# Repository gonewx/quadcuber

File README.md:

> 最终机械版：**501 步、882 件**（64 件底盘＋668 件四臂＋150 件支承与重力复位杠杆）。
> [整机 3D](generated/site/index.html) · [501 步组装](generated/site/integrated-assembly.html) · [完整 PDF](generated/mechanical/manual/manual.pdf) · [最终 BOM](generated/mechanical/final-BOM.csv) · [生成源码与重建](mechanical/README.md)
> **GitHub 仓库为主源码，Sites 仅用于发布。** 当前机械设计见 `mechanical/`；早期 v4 改装资料保留用于历史追溯。实体装配、承载、重力回落与带电联锁仍待验收。

# quadcuber

四机械手乐高魔方机器人（参考 CubeStormer 3 的思路），目前包含**动作规划器**、**模拟器**，以及**单臂原型的 Pico 测试程序**。

* 规划器：把求解器给出的转动序列（如 `R U R' U'`）翻译成 4 个机械手的动作序列，并使总耗时最短。

* 模拟器：在 54 个贴纸的魔方模型上按物理动作逐步重放，检查每一步是否满足机械约束，以及最后魔方是否还原。

* 单臂测试程序（`firmware/pico/`，MicroPython）：测机械手转 90° 的耗时、到位精度和夹持可靠性，结果汇总后替换规划器的耗时估算值。接线和测试步骤见 [docs/single\_arm.md](docs/single_arm.md)，乐高机械手的结构思路和尺寸要求见 [docs/arm\_concept.md](docs/arm_concept.md)，**搭建说明书**见 [generated/site/integrated-assembly.html](generated/site/integrated-assembly.html)（501 步最终整机版，总入口 [docs/lego/index.html](docs/lego/index.html)）。

规划器纯 Python 实现，不依赖第三方库，可以在 PC 或树莓派 Zero W 上运行。

## 电路与硬件验证

当前手焊板为 **[B1 底板](electronics-b1/README.md)**：99×99mm 双层板，插装 Pico H，其余元件手焊。PCB 和零件已到手，按 **[B1 焊接与首次上电指南](docs/b1-soldering-guide.md)** 装配，配合[元件位置图](generated/electronics-b1/assembly.png)和[手焊 BOM](generated/electronics-b1/bom-hand-solder.csv)。焊接、编码器电平、供电及带载仍待实测。

[A1 集成板](electronics/README.md)及其[工程首板送厂包](generated/electronics/engineering-first-board/README.md)保留作历史资料；其板载 RP2040、双面 SMT、自焊18件和专用固件流程不适用于 B1。

打开[当前接线：原 R／新 R+L（条件式）](generated/wiring/direct-breadboard.html)，在同一页面切换图、表和下载，默认显示原 R。适用条件见[电路总览](docs/wiring/README.md)；[历史单臂总览](generated/wiring/index.html)和[可选单臂洞洞板](generated/wiring/perfboard.html)保留作参考。EV3 大马达＋DRV8833 的空载闭环已通过，范围见[实测记录](docs/single_arm-results.md)；这不等于 v4 机械头、舵机、带魔方动作或四臂供电已验收。接下来需要实物标定和分级测试。

当前硬件：EV3 大马达、DRV8833（名义 9V，实测不得超过 10.8V）、每路 10kΩ/20kΩ 编码器分压（`ENC_PULLUP = False`）、灰色 270° Geekservo。调试时 Pico 由 USB 供电，舵机由独立 5V 降压供电，所有模块共地。接线以 `wiring/spec.py` 及其生成图表为准。

固件的开／合端点及安全工作区间（`SERVO_OPEN_US`、`SERVO_CLOSE_US`、`SERVO_MIN_US`、`SERVO_MAX_US`）默认均为 `None`，`SERVO_CALIBRATED = False`。未完成实物标定时，普通动力命令会拒绝执行；仅在确认无魔方、机构全行程自由且供电接线已核验后，可显式进入 `motor_test unloaded` 做空载马达验证，该模式不允许舵机开合或带载测试。按[单臂标定步骤](docs/single_arm.md#servo-calibration)先脱开连杆、声明手动会话，再逐步测量舵机端点及安全区间，最后人工记录 `v4`／`R` 标定身份并启用标志。启动不发送舵机脉冲，但不能保证上电硬件不抖动；旧脉宽和 CAD 角度不能充当实测值。

舵机时序另行确认：默认 `SERVO_MOVE_MS = None`、`SERVO_TIMING_CONFIRMED = False`。端点、安全区间和身份确认后，人工选定保守的临时等待时长（1～5000ms 整数，不沿用旧 120ms），仅用单次 `open` / `close` 录像测量，确认完全停稳才发下一条。此时 `grip`、`cycle` 和普通旋转仍被锁定，显式空载马达模式是例外。实测完整开／合的较慢值加余量后回填等待时间、设置 `SERVO_TIMING_CONFIRMED = True`，上传并 Ctrl+D 重载，才进入连续及联合测试；机构或供电变化后重新确认。

```bash
python wiring/build.py          # 生成全部电路文档及图纸
python wiring/build.py --check  # 检查配置、网络和生成文件是否同步
```

## 机器模型

```
        B
        |
  L --[魔方]-- R      U 面朝上（留给摄像头），D 面朝下；这两个面没有机械手
        |
        F
```

* 4 个机械手分别位于 R / L / F / B 方向，每个机械手可以**夹紧 / 松开**，也可以**旋转**（90° 的整数倍）。
* 夹爪是一根横跨面中间一行或一列的“夹条”。机械手角度为偶数（包括 0）时夹条竖直，为奇数时水平。
* 约束（实现见 `quadcuber/machine.py` 的 `Machine.check`）：
  1. **支撑**：任何时刻 L、R 都夹紧，或 F、B 都夹紧，否则魔方会掉落。
  2. **拧面**：拧某个面时，与它垂直且夹紧的机械手，夹条必须竖直，否则会挡住转动；并且至少有一个这样的机械手夹紧，用来固定中间层。相对的两个面可以在同一步同时拧。
  3. **整体翻转**：一对机械手夹紧并同向旋转，把 U/D 面换到有机械手的位置；此时另一对必须松开。
  4. **空转**：松开的机械手可以旋转来调整夹条方向，并且可以和其他动作同时进行。
  5. **相邻臂避碰（v4 必须）**：相邻两臂不能同时水平；任一臂旋转时，相邻两臂必须保持竖直且不在同一步旋转。拧面、空转、整体翻转以及经过水平位置的 180° 动作都适用，松开夹爪不能解除这条约束。
  6. **角度限制（可选）**：`angle_limit` 默认仍为 `None`。v4 舵机固定在平台上，不随机械头转动，不因舵机缠线强加角度上限。其他需要累计角度边界的结构可显式使用 `--angle-limit`。

`Machine()` 和 CLI 的 `plan` / `bench` 默认使用 `profile="v4"`，强制启用 `no_adjacent_horizontal=True`，不能在 v4 profile 下显式关闭。`Machine(profile="generic")` / `--profile generic` 保留旧抽象模型，仅供明确的非 v4 用途；generic 仍可用 `--no-adjacent-horizontal` 增加约束。规划器的检查不代替实物避让、刚度、保持力与耗时标定。

## 使用

```bash
# 规划一个转动序列，并在模拟器中验证
python -m quadcuber plan "R U R' U' F2 D"

# 同时输出 JSON，供下位机（Pico）执行
python -m quadcuber plan "R U R' U'" --json plan.json

# 随机 20 步序列的统计，--compare 同时对比“不做任何并行”的基准方案
python -m quadcuber bench --count 20 --compare

# 使用实测的动作耗时
python -m quadcuber bench --timing timing.json

# 仅用于非 v4 结构的旧抽象模型；不要用它驱动当前 v4
python -m quadcuber plan "R U R' U'" --profile generic
# generic 也可显式启用更严格的相邻臂约束
python -m quadcuber bench --profile generic --no-adjacent-horizontal
```

`timing.json` 的字段见 `quadcuber/machine.py` 中的 `Timing`，单位为秒。**默认值是估算值**，搭好单臂原型后应替换成实测值（可以用 `python -m quadcuber armlog arm.log -o timing.json` 从单臂测试日志生成）：

```json
{"turn90": 0.18, "turn180": 0.30, "open": 0.10, "close": 0.10,
 "rotate90": 0.15, "rotate180": 0.25, "cube90": 0.22, "cube180": 0.35}
```

## 规划算法

* 在（已完成的转动，机器状态）空间中做 A\* 搜索，代价为总耗时。每一步是一组同时执行的动作。
* 连续的同轴转动（例如 `R L'`）会合并为一组，可以按任意顺序执行，也可以同时执行。
* 默认使用**滚动窗口**：每次对接下来的 4 组转动求最优，只采用前 2 组的动作。实测比全局最优（`--full`）只慢 1~2%，但速度快得多。
* 有角度限制时，先按不限角度规划，再用动态规划选择旋转方向（必要时顺带退绕）；只有无法满足限制的窗口才做完整的受限搜索。

历史旧抽象模型在开发机上的测量（30 个随机 20 步序列、估算耗时参数，未包含当前默认的 v4 相邻臂约束；不是 v4 实物数据）：

| 情况 | 动作总耗时（平均） | 规划 CPU 时间（平均） |
| --- | --- | --- |
| 不限角度 | 7.9 s | 0.8 s |
| 角度限制 ±180° | 8.0 s | 11 s |

角度受限时规划仍然偏慢，树莓派 Zero W 上预计还要慢一个数量级。建议优先采用不需要角度限制的夹爪结构。

## 测试

```bash
python -m unittest -v
```

测试覆盖：魔方模型、各条机器约束，以及随机序列经规划后能在模拟器中还原；Pico 固件在模拟环境（马达模型 + PIO 解释器，`tests/pico_sim.py`）中的编码器计数、位置控制和各条测试命令；日志汇总工具。

## 目录

| 路径 | 内容 |
| --- | --- |
| `quadcuber/cube.py` | 贴纸魔方模型、转动记号解析 |
| `quadcuber/machine.py` | 机器状态、动作、约束、耗时参数 |
| `quadcuber/planner.py` | 动作规划器 |
| `quadcuber/simulate.py` | 模拟器 / 验证 |
| `quadcuber/armlog.py` | 单臂测试日志汇总，生成 `timing.json` |
| `quadcuber/__main__.py` | 命令行 |
| `firmware/pico/` | 单臂测试程序（MicroPython）：配置、PIO 编码器、马达/舵机驱动、位置控制、串口命令行 |
| `docs/single_arm.md` | 单臂原型的接线、测试步骤和待验证假设 |
| `docs/arm_concept.md` | 乐高机械手的概念设计：叉子 + 滑块结构、关键尺寸、单臂测试的魔方固定方法 |
| `electronics/`、`generated/electronics/` | 四臂集成 PCB 的 KiCad 源码、BOM、检查与制造预览 |
| `wiring/`、`generated/wiring/` | 接线规范和生成程序；对应标准图纸输出 |
| `docs/perfboard.md` | 可拔插洞洞板设计：逐孔安装、镜像焊接图、模块排针座及上电验收 |
| `docs/lego/` | 库存和兼容导航；历史原件通过固定 Git 提交查阅 |
| `mechanical/`、`web/`、`tools/` | 机械／网页源码及少量打包、重建入口 |
| `mechanical/` | 最终机械模型、501 步图解与 PDF、生成器、离线阅读器和 Sites 页面源码 |
| `tests/` | 控制及最终机械一致性测试 |

## Prompts

* gpt-6-astra high

现在的设计还是不理想, 设计结构复杂,但实际效果看着也不行. 我有思路需要你评估和验证: 需要在上一版本整体结构上主要优化方向是推杆到夹指的传力,要能将舵机的力量传递到夹指前端, 而不是像现在这样中间的连接是无摩擦销,导致力量无法传递, 所有现在的夹指整体的平行的设计理念 ,也导致总是间隙, 因为乐高结构和尺寸决定了现在这样的设计必然无法夹紧. 所以夹紧状态应该是现在的夹指部分不用完全 平行于魔方, 但夹指前端必须有新的结构件能自然贴合魔方, 达到夹紧的效果.

## 源码与输出

`mechanical/`、`wiring/`、`electronics/`、`web/` 分别维护机械、接线、集成PCB和网页源码；`generated/` 保存唯一标准输出；`dist/` 为不入 Git 的网站／离线／源码包。`docs/` 保存人工说明及原始实测证据，`tests/` 保存回归与独立基准；运行库 `quadcuber/` 和固件 `firmware/` 原位保留，不新增 `src/`。

运行 `python tools/build_distribution.py` 后可打开离线包，或从仓库根启动 `python -m http.server 8000` 浏览 `generated/site/index.html`。网站下载提供紧凑源码／模型包；图解与 PDF 另下。`dist/downloads/quadcuber-source-complete.zip` 是含完整图解的独立重建包；构建不发布。历史方案见 [历史索引](docs/history.md)。

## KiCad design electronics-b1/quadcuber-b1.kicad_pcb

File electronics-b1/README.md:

# B1 底板（KiCad 工程）

方案和取舍见 [docs/b1-carrier-board.md](../docs/b1-carrier-board.md)。本目录是 B1 唯一的源文件目录，与 A1（`../electronics/`）完全独立，不引用 A1 的库文件。

- 2 层 FR-4，99×99mm，1.6mm，1oz。元件全部放在顶面，尽量用贴片件（0805 及以上、SOIC/SOT-223/TO-263/HSOP），自己用热风枪和烙铁手焊。只有排针、Pico 排母、DC 插座和 EV3 插座是通孔件。
- 树莓派 Pico H 插在两排 1×20 排母上，USB 朝板子上边。引脚与 `wiring/spec.py` 的 `ARMS` 一致，固件不用改。
- 四个 EV3 插座在下边，从左到右依次是 R / L / F / B。每个插座上方是该臂的舵机排针，自下而上为 G / + / S。
- 接口丝印（2026-10-20 补）：舵机排针右侧逐针印 `G` / `+` / `S`；J2 右侧印 `GND` / `TX` / `RX`、下方印 `UART`（不是舵机口）；EV3 插座背面在第 1 针（M1）旁印 `1`。**已生产的 B1 实物没有这些丝印**（首测时舵机插反、插进过 J2），实物上用记号笔在每个舵机排针的 G 针旁点标记。

## 文件

| 文件 | 作用 |
|---|---|
| `circuit.py` | 元件、网络和摆放位置的唯一来源 |
| `silk.py`、`label_interfaces.py` | 接口丝印（数据在 `circuit.py` 的 `SILK`/`REF_MOVES`）。`generate.py` 生成时就加上；`label_interfaces.py` 给已布线的 PCB 补加，只动丝印文字，可重复运行 |
| `generate.py` | 生成符号库、原理图、工程文件和未布线的 PCB。预先画好并锁定两条电源主干（VM 底层 2mm、舵机 5V 顶层 1.5mm），并给每个贴片接地脚加就近的接地过孔 |
| `route.py` | 导出 DSN（带显式线宽），用 freerouting 布线，导入 SES；填充两面地铜，再打地缝合过孔 |
| `build.py` | ERC/DRC（有错误就中止）、网表、Gerber+钻孔 ZIP、手焊 BOM、预览 SVG |
| `test_b1.py` | 不依赖 KiCad 的引脚映射回归测试：Pico 官方引脚、四臂引脚、电源路径、网表与 PCB 一致 |
| `lib/B1.pretty`、`lib/3dmodels` | 自包含的封装和 3D 模型：KiCad 标准库副本，以及 A1 已核对的 DRV8871、EV3 封装副本。3D 模型用 `${KIPRJMOD}` 引用，KiCad Lite 不装标准 3D 库也能显示 |

## 重建

装配图导出需要 Python 包 `cairosvg`（`python3 -m pip install cairosvg`）及系统 Cairo 运行库。构建会同时生成带固定深色背景的 SVG 和 2400×2400 PNG，便于直接打开查看。

```sh
export KICAD_APP_RUN=<KiCad 10.0.7 AppImage 解包目录>/AppRun
$KICAD_APP_RUN python3.11 electronics-b1/generate.py
$KICAD_APP_RUN python3.11 electronics-b1/route.py <freerouting-2.1.0.jar> 30
$KICAD_APP_RUN python3.11 electronics-b1/label_interfaces.py   # 只改丝印时从这一步开始，不用重新布线
python3 electronics-b1/build.py
python3 -m unittest electronics-b1/test_b1.py -v
```

freerouting 2.1.0 的下载地址和 SHA256 见 `../electronics/toolchain.json`。自动布线每次的结果可能略有不同；重新布线后必须重跑 `build.py` 和测试。

## 当前检查结果（2026-10-20，补接口丝印后）

- ERC：0 错误，0 警告。
- DRC：0 错误，0 个未连通焊盘。另有 19 条警告：16 处丝印重叠（位号文字压在相邻元件上；新加的接口丝印没有重叠），3 处是锁定电源主干的端点悬空。都不影响制板。
- `test_b1.py` 6/6 通过（新增：每条接口丝印都在 PCB 上，且与对应网络的焊盘同一行）。

## 焊前要核对的实物

1. **DC 插座**：封装用的是 KiCad 的 `BarrelJack_Horizontal`，后脚到前脚 6mm，侧脚偏出 4.7mm。焊前用卡尺核对手上的 DC-005，并试插匹配电源插头核通断；对不上先排查适配。
2. **EV3 插座**：同批的要够 4 个。

3. **L1 电感**：采购记录为 TDK SLF12575T-330M3R2-PF，板上是通用封装；焊前确认实际端子与焊盘搭接，详见焊接指南。

其他贴片件也需按 BOM 核型号、封装、数值及极性，不能只按外形大小装配。

## 焊接与上电

完整步骤见 **[B1 底板焊接与首次上电指南](../docs/b1-soldering-guide.md)**，包含正面元件图、逐颗极性、分阶段焊接、测点及验收记录。用户已于 2026-10-16 确认 PCB 和零件到手，实板焊接和上电尚待记录。

实际操作直接照[焊接批次总表](../docs/b1-soldering-guide.md#soldering-batches)逐行完成：每批列出工具、耗材、全部位号和数量，可勾选检查。

本次顺序：低矮贴片件（IC、电阻/陶瓷电容、二极管/保险丝）分区点锡浆并热风焊接 → L1 热风焊接 → 烙铁焊电解 → 烙铁焊排针排母及插座。Q1 和 DRV8871 都可优先用热风，区别是 Q1 只需给八脚上浆，DRV8871 还需给中心散热焊盘上浆。CSV 中原“焊接顺序”列仅保留作类别排序，操作以指南为准。DRV8871 的底部散热焊盘必须焊接；U1 散热片接地，U2 散热片接 5V_LOGIC。

首次上电先不插 Pico、不接 USB、电机或舵机，使用限流 0.3A 的稳压 9V 电源，按指南量 VM、两路 5V 和 VSYS。EV3 六路断电通断与编码器电平检查必须在连接 Pico 输入之前完成：10kΩ/20kΩ 分压在输入 5V 时计算值为 3.33V，不能假定必然低于 3.3V，超出指南筛查条件时先处理分压，不插 Pico。

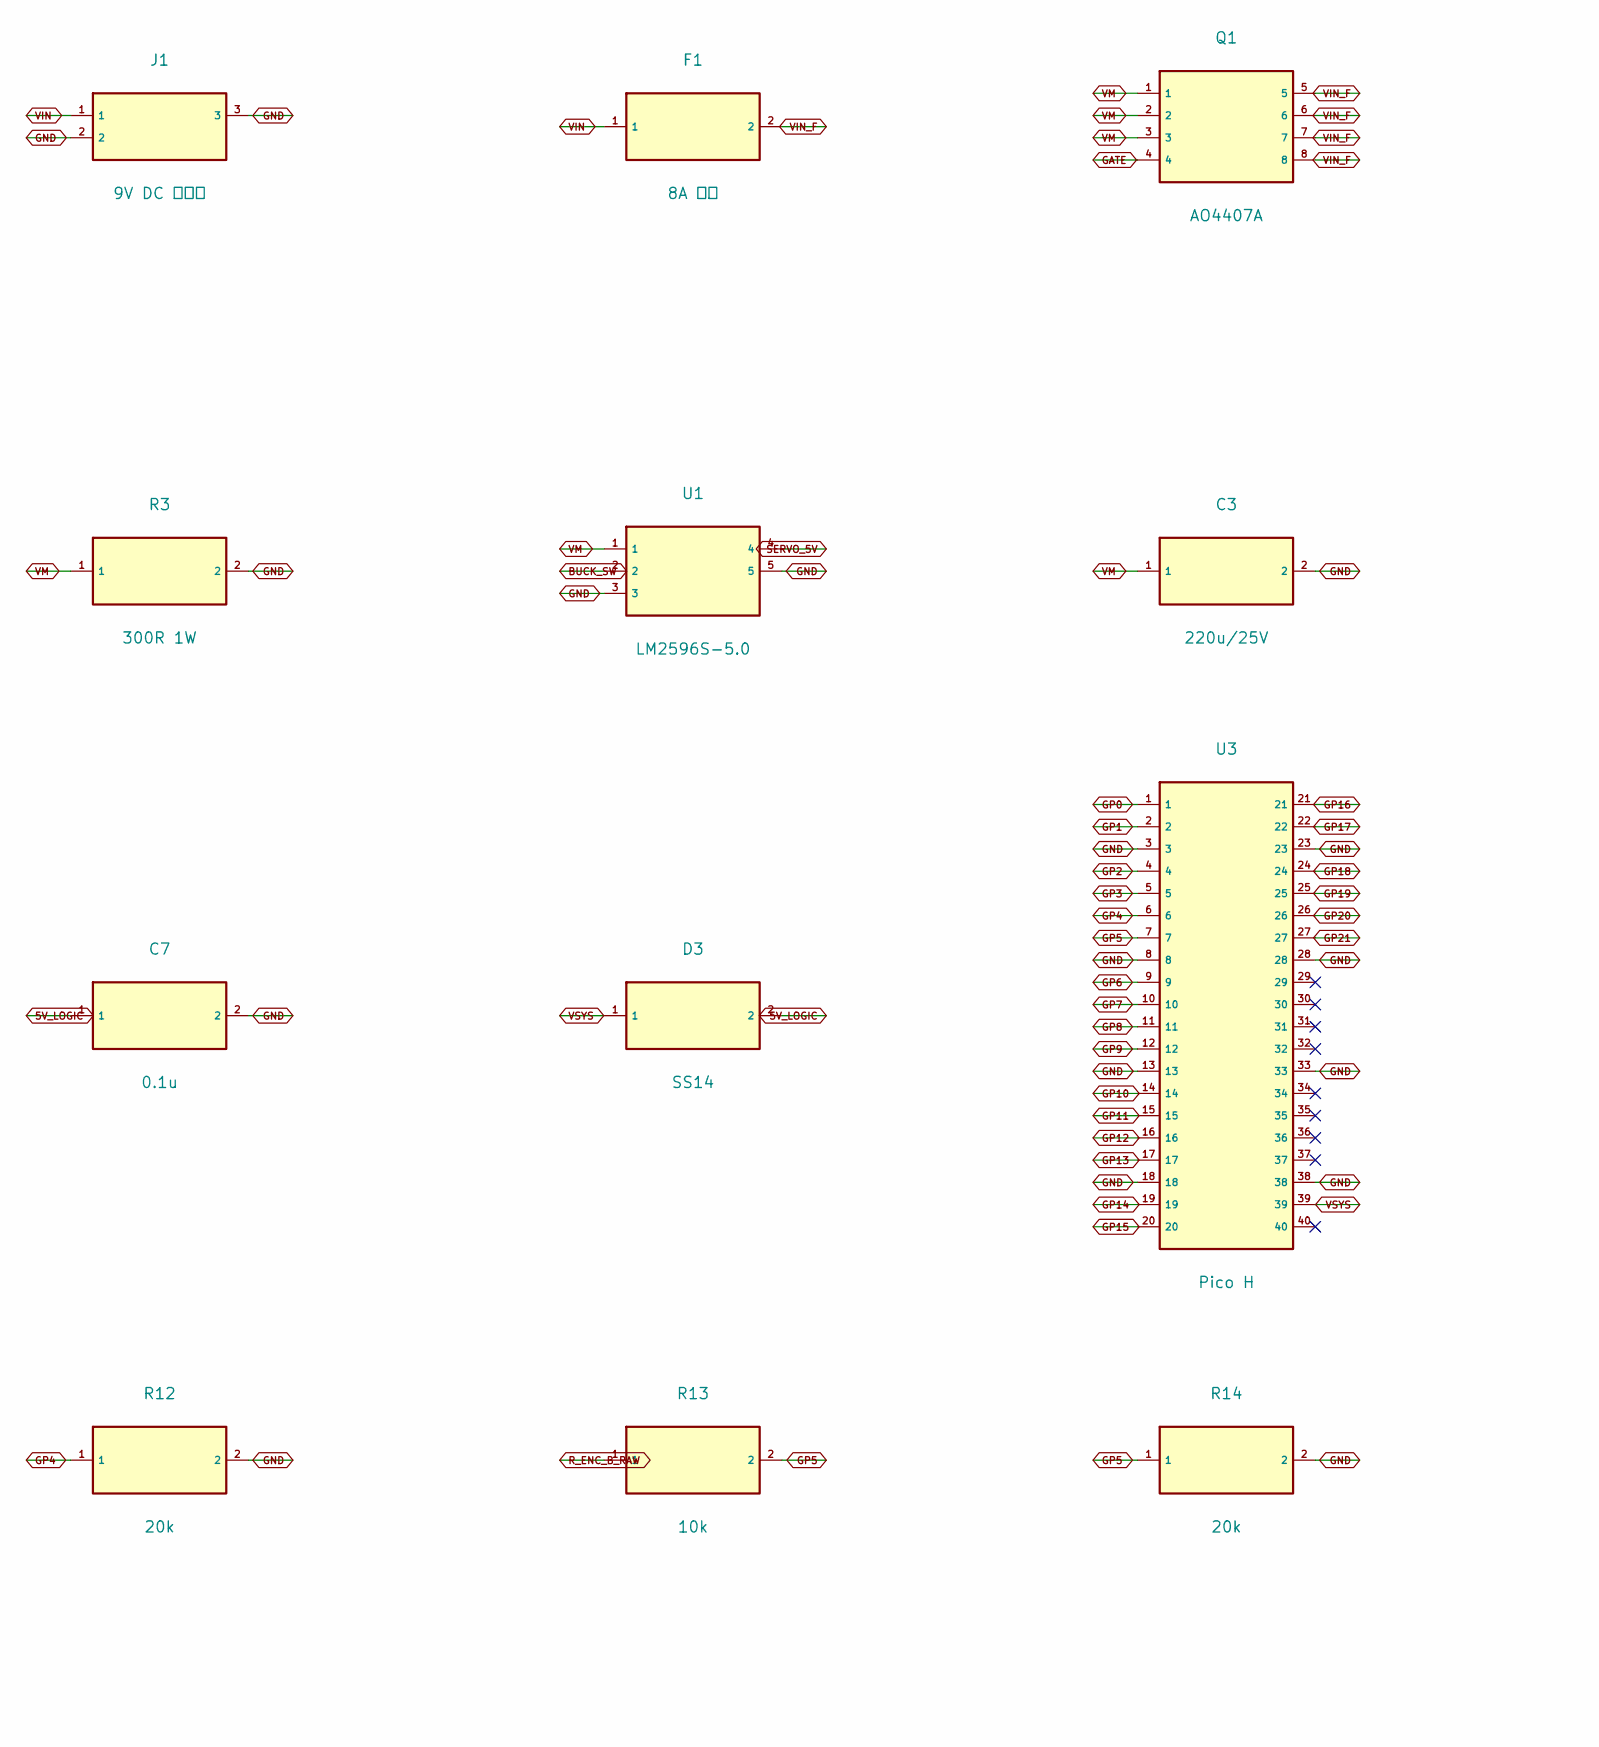
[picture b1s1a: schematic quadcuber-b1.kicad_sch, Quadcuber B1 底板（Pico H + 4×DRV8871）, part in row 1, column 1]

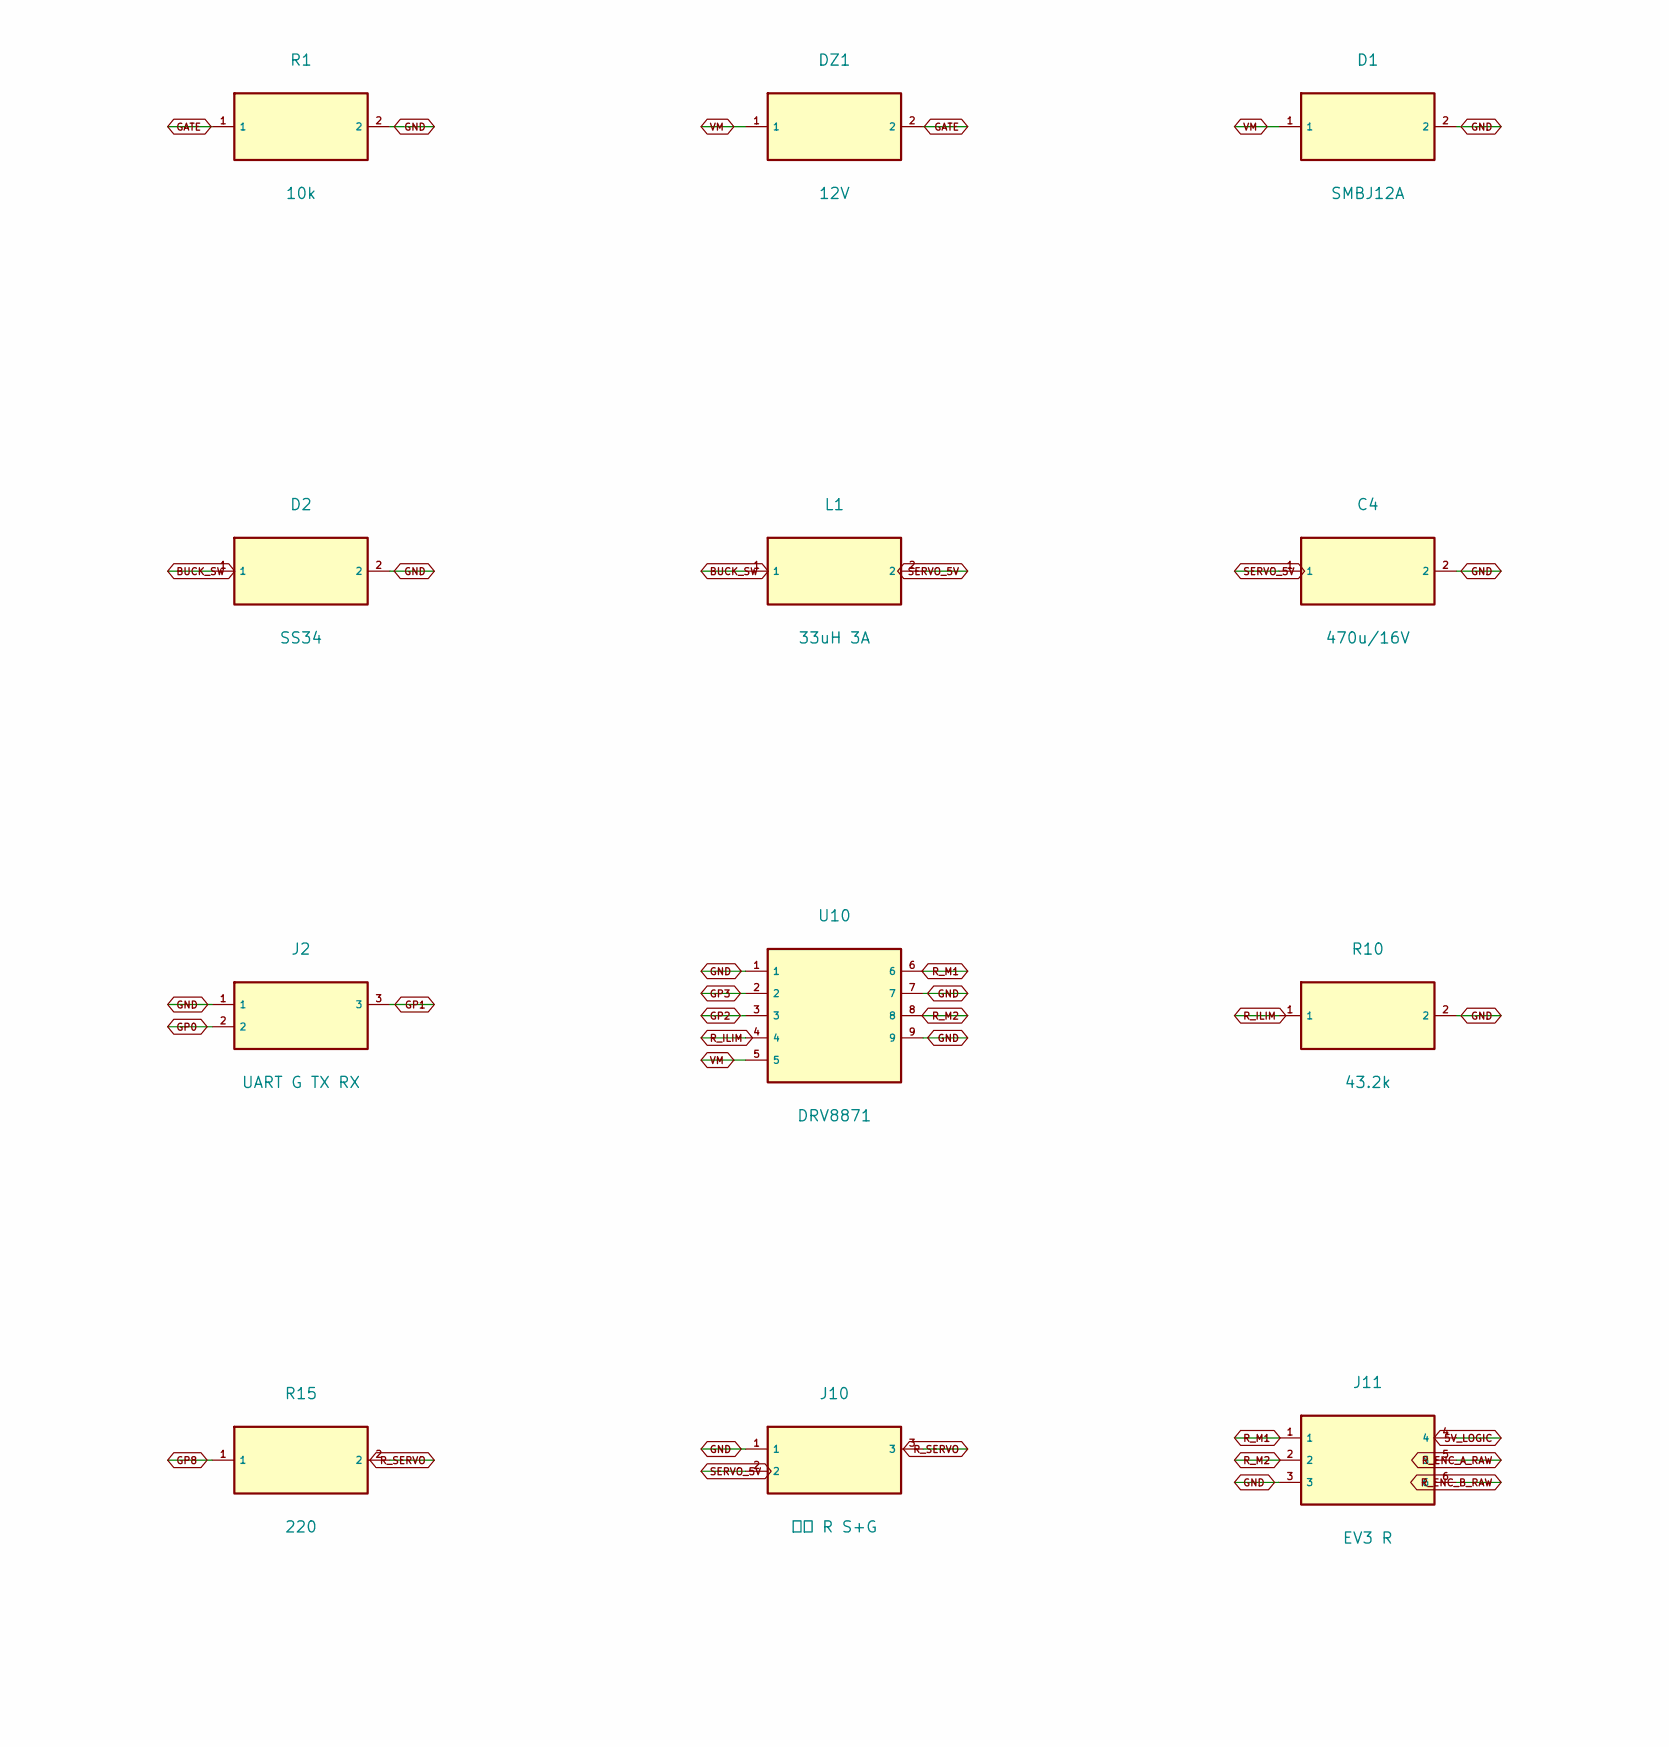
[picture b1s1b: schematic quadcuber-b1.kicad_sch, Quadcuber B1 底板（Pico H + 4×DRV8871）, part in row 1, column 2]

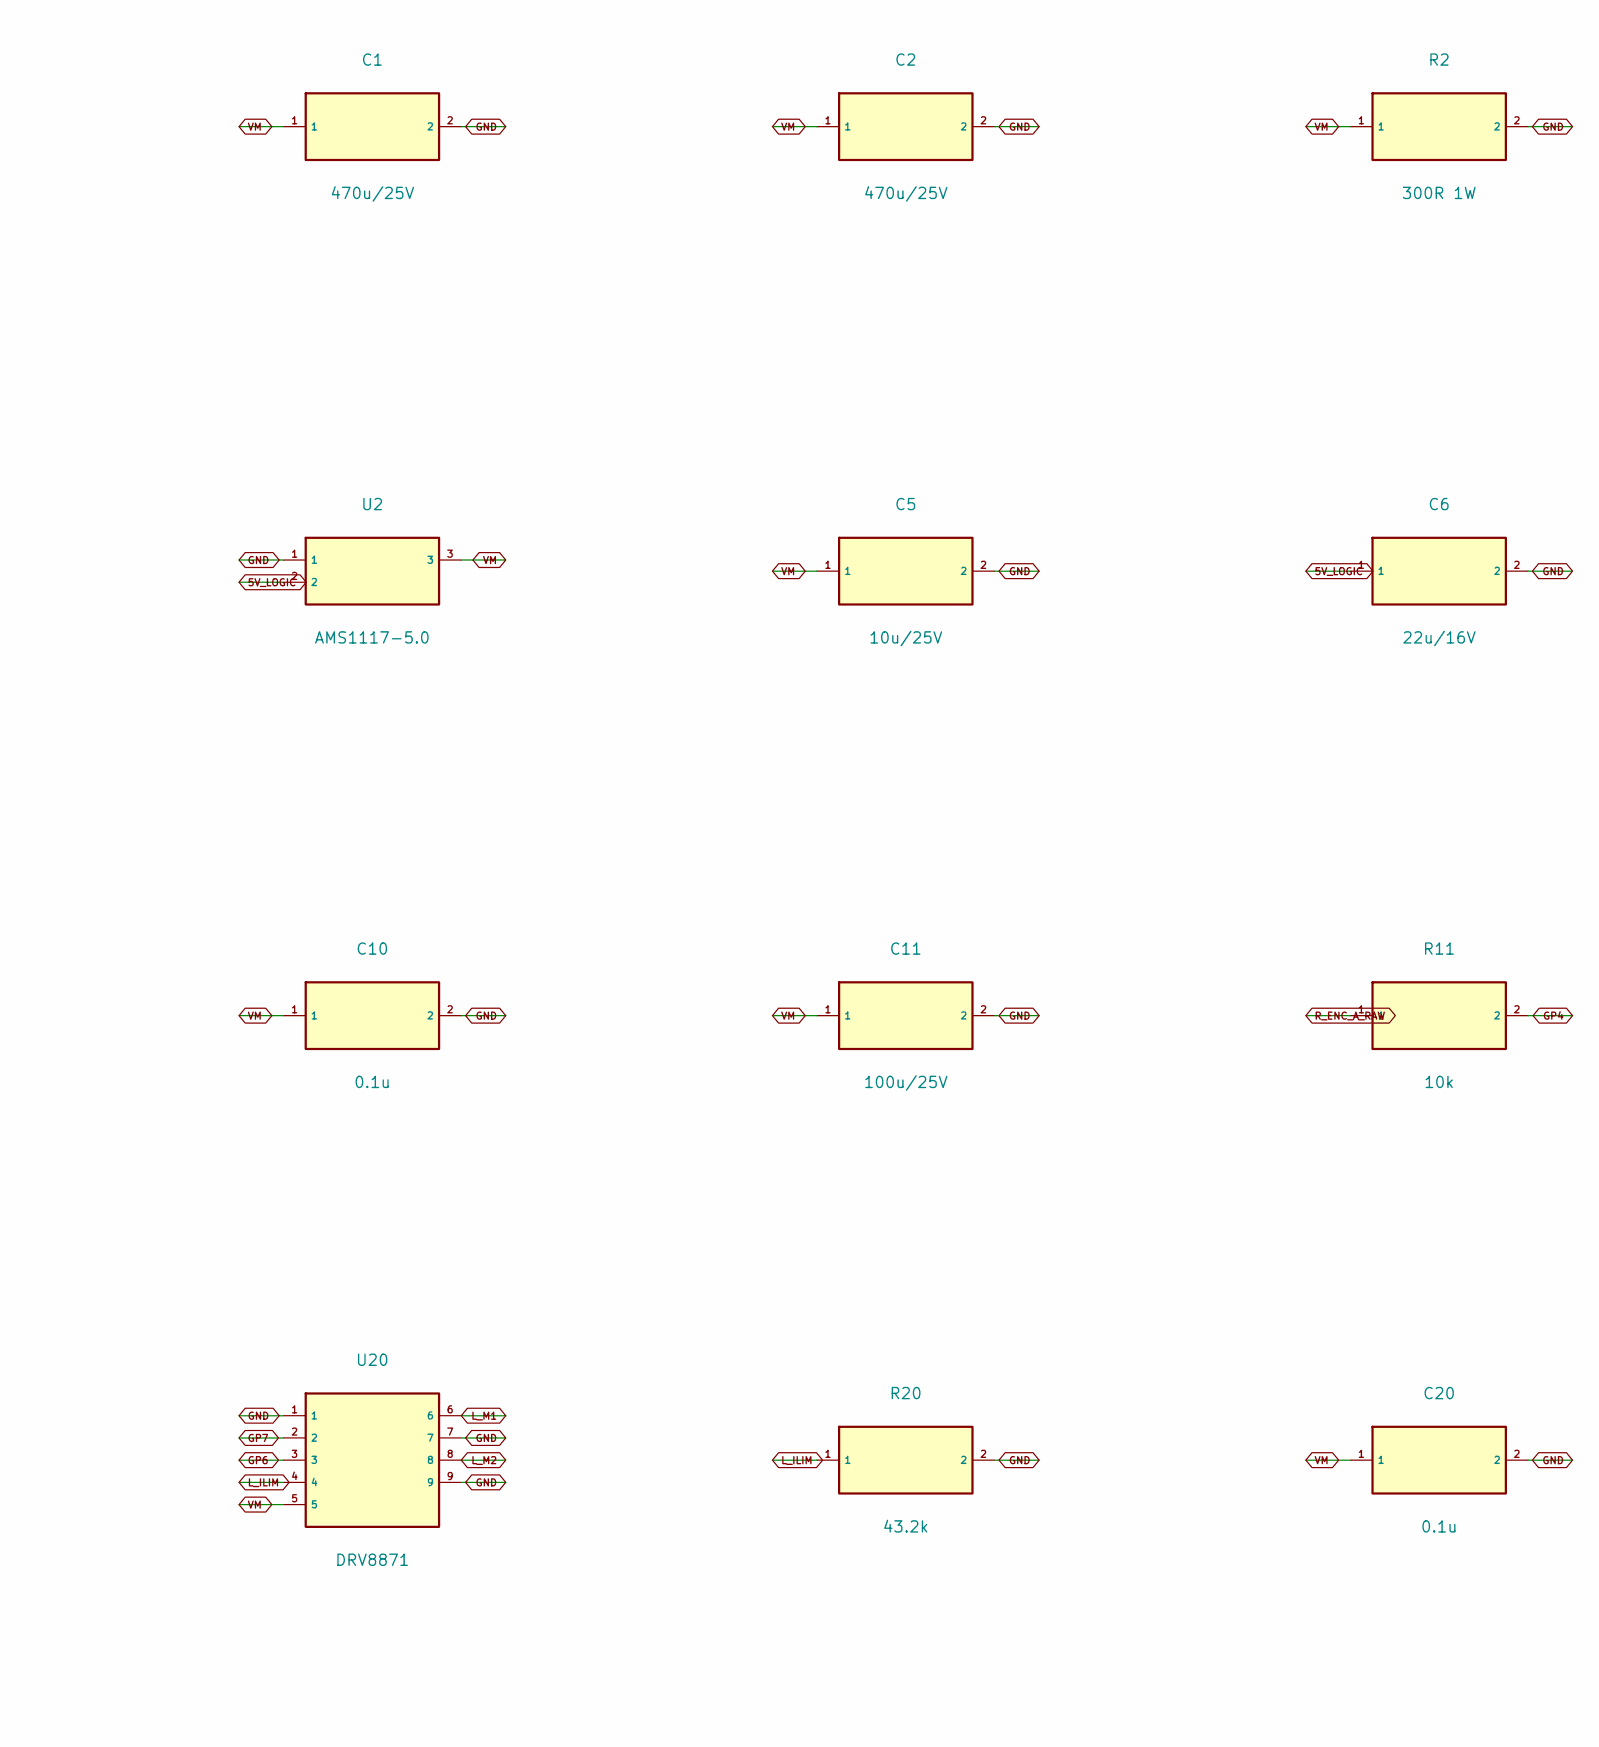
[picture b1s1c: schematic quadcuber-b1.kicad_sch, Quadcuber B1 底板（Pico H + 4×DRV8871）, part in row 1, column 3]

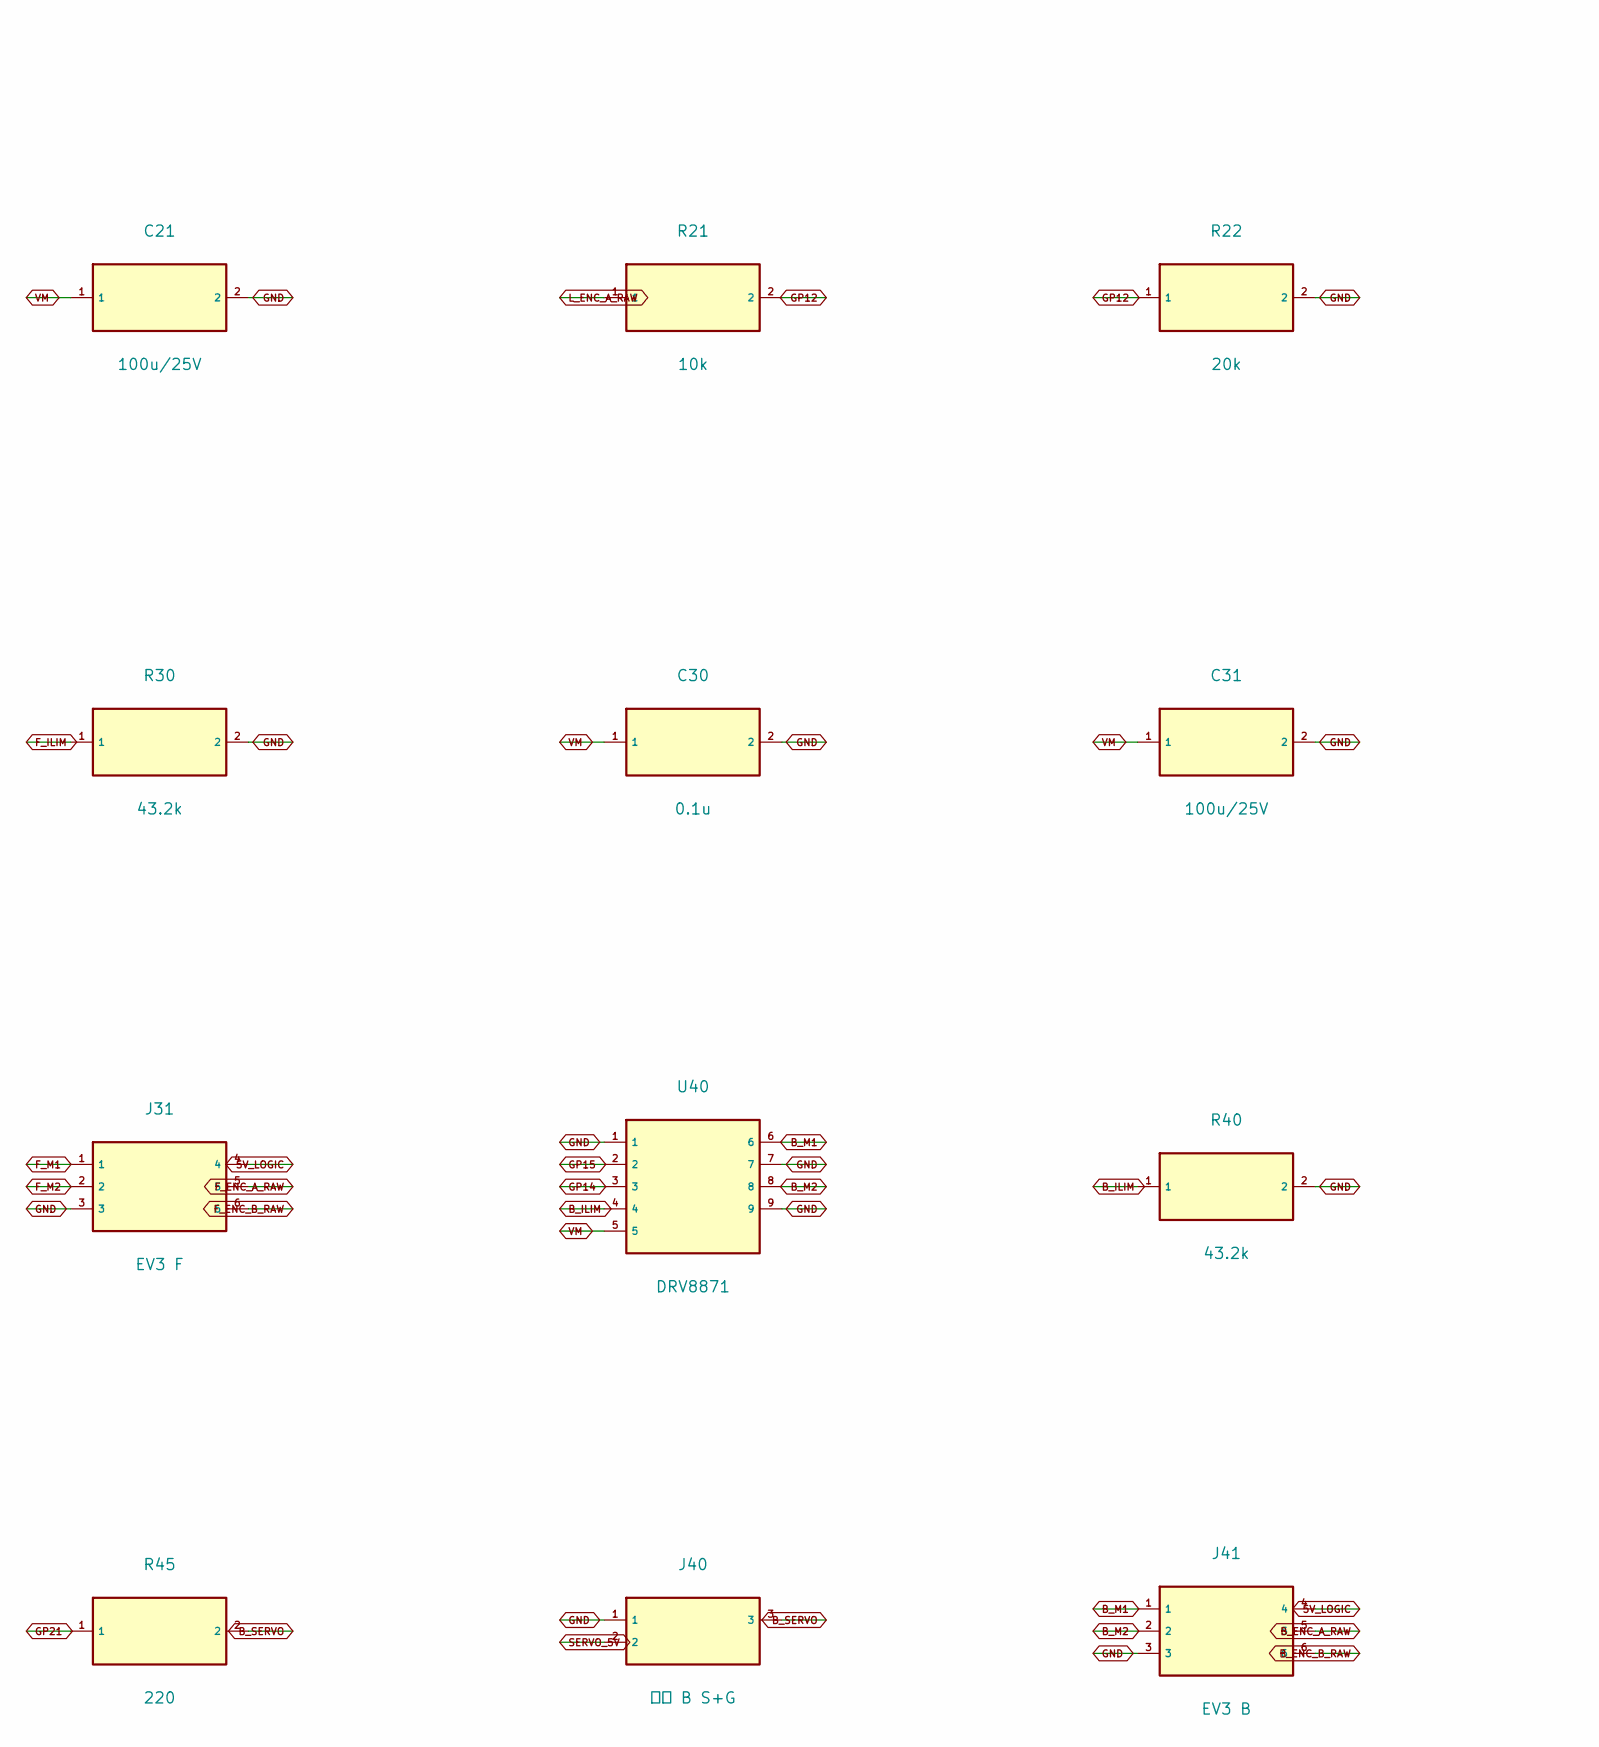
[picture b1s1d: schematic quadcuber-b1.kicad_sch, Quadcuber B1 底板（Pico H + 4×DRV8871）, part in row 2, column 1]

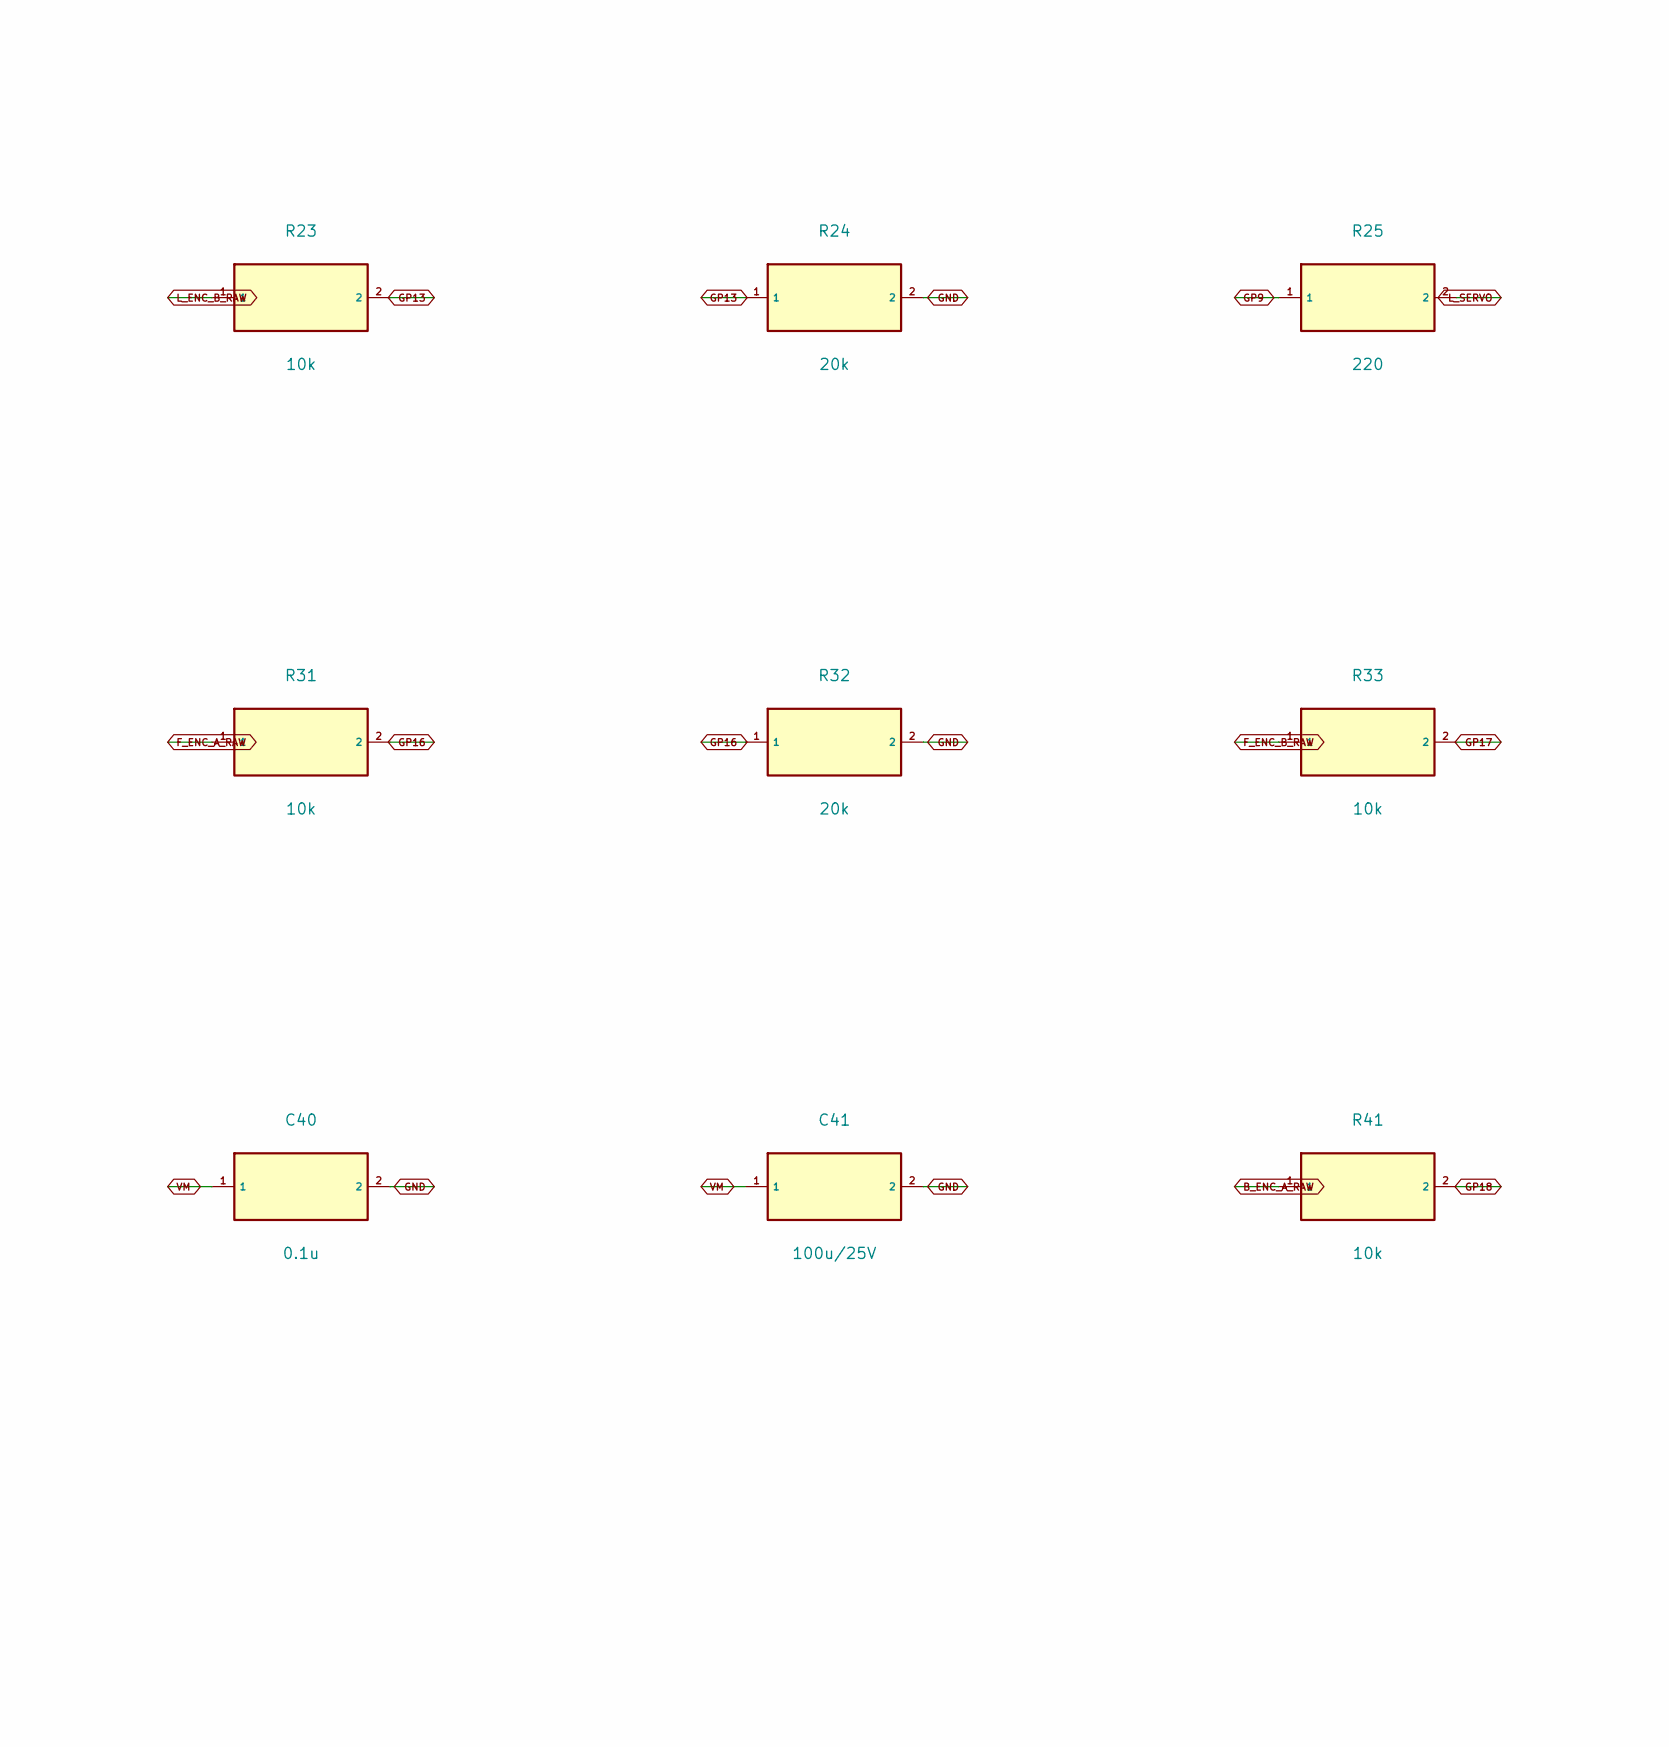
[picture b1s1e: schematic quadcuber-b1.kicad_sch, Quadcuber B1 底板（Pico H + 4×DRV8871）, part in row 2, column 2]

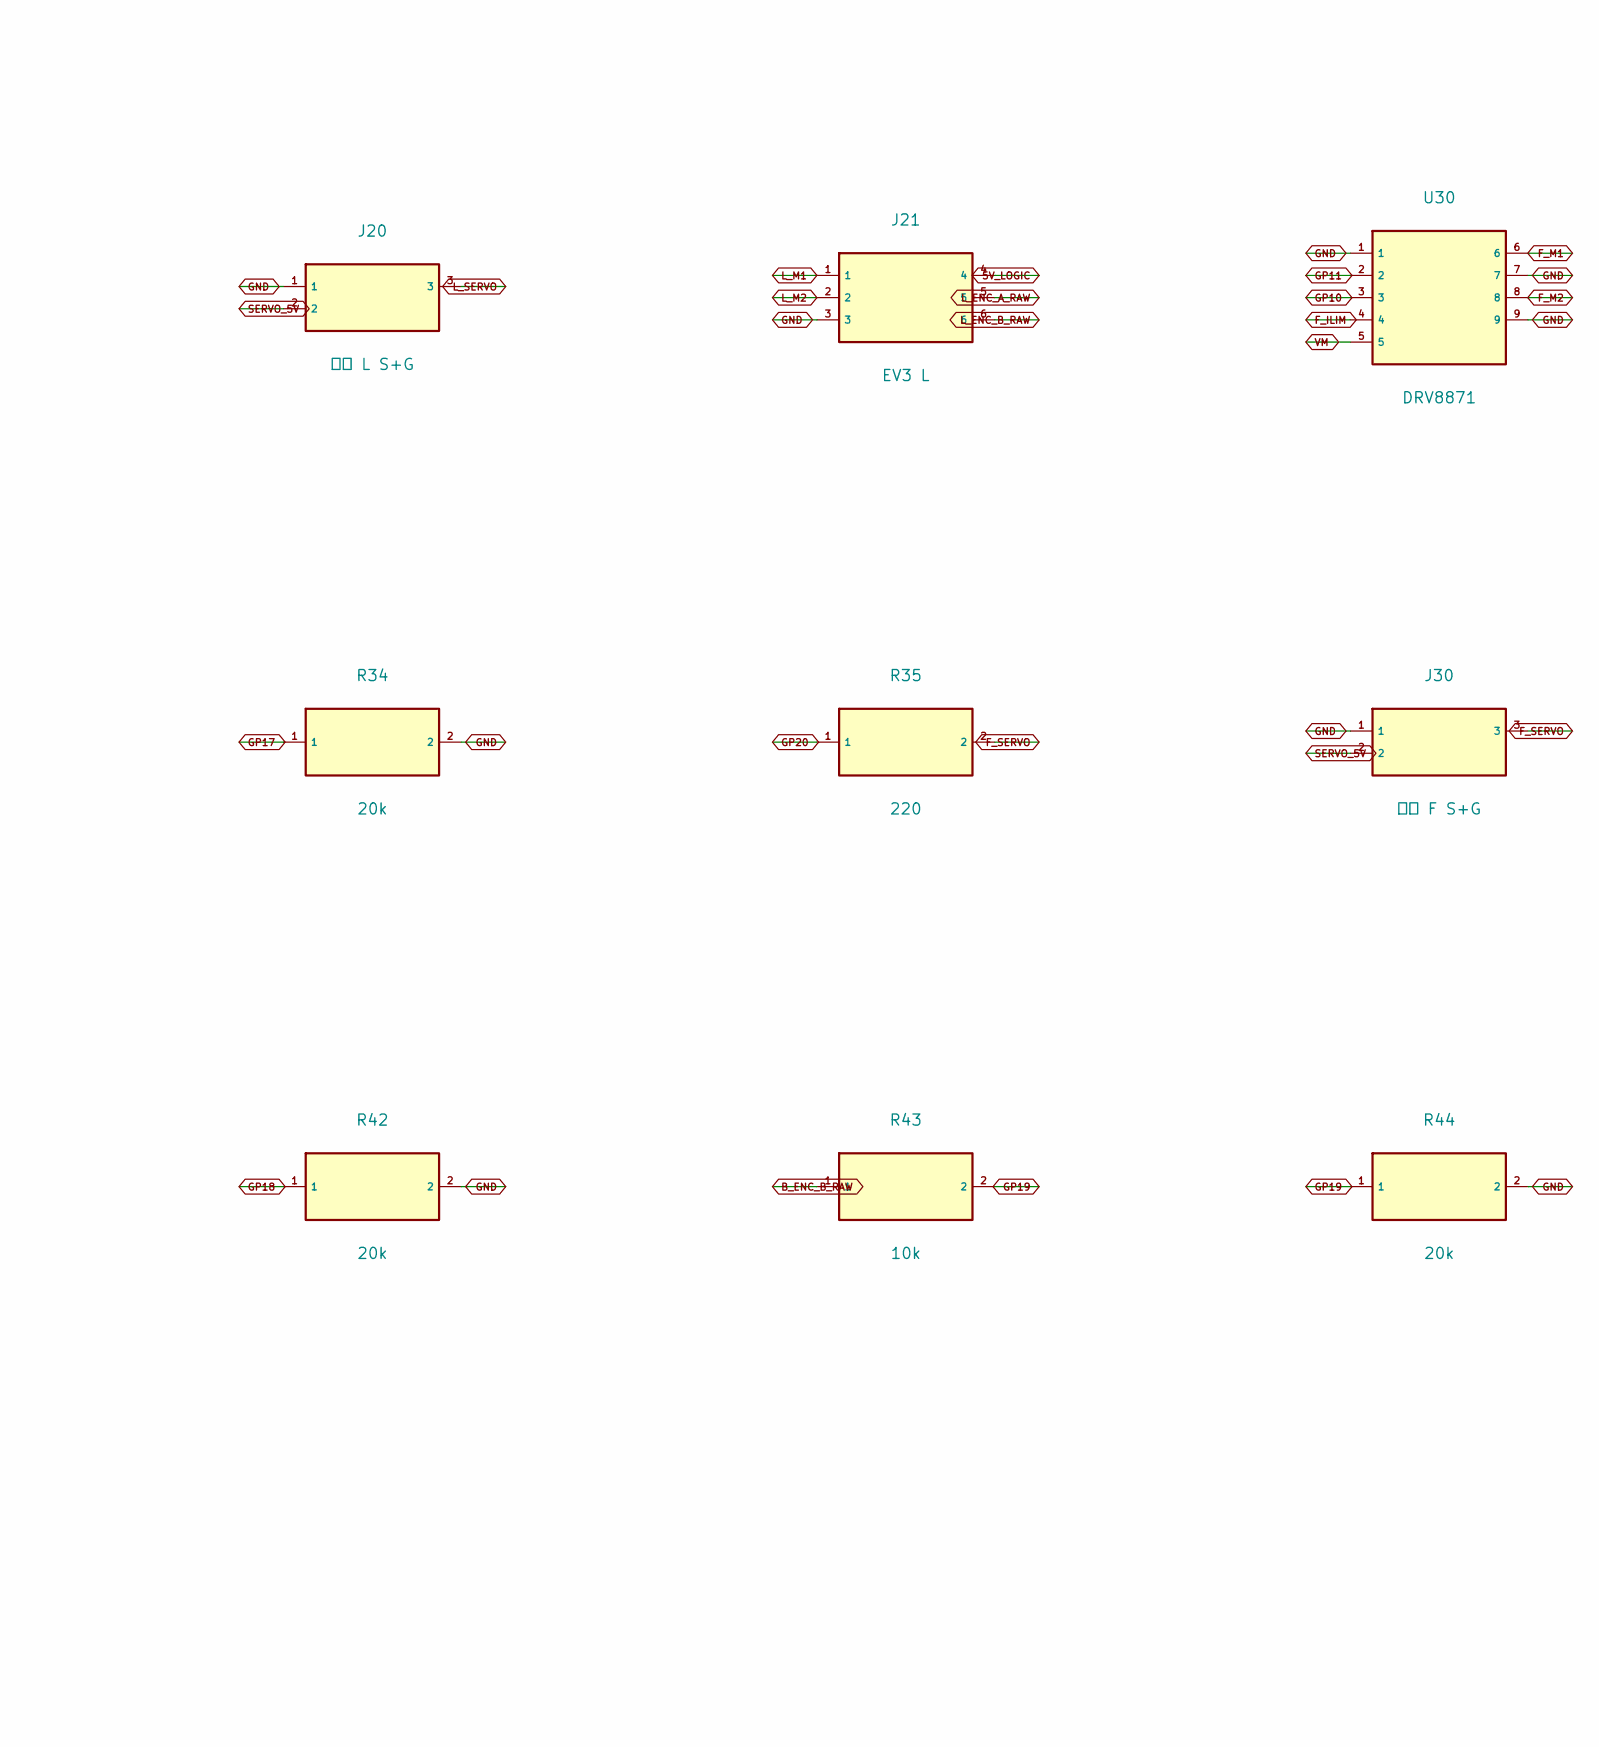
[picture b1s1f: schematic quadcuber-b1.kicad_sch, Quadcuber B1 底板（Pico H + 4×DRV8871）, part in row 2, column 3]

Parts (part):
C1, C2: 470u/25V; CP_Elec_10x10.5
C3: 220u/25V; CP_Elec_8x10.5
C4: 470u/16V; CP_Elec_8x10.5
C5: 10u/25V; C_0805_2012Metric_Pad1.18x1.45mm_HandSolder
C6: 22u/16V; C_0805_2012Metric_Pad1.18x1.45mm_HandSolder
C7, C10, C20, C30, C40: 0.1u; C_0805_2012Metric_Pad1.18x1.45mm_HandSolder
C11, C21, C31, C41: 100u/25V; CP_Elec_6.3x7.7
D1: SMBJ12A; D_SMB_Handsoldering
D2: SS34; D_SMA_Handsoldering
D3: SS14; D_SMA_Handsoldering
DZ1: 12V; D_SOD-123
F1: 8A 慢断; Fuse_1206_3216Metric_Pad1.42x1.75mm_HandSolder
J1: 9V DC 中心正; BarrelJack_Horizontal
J2: UART G TX RX; PinHeader_1x03_P2.54mm_Vertical
J10: 舵机 R S+G; PinHeader_1x03_P2.54mm_Vertical
J11: EV3 R; EV3_Socket_UserDrawing
J20: 舵机 L S+G; PinHeader_1x03_P2.54mm_Vertical
J21: EV3 L; EV3_Socket_UserDrawing
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
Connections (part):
5V_LOGIC: C6.1, C7.1, D3.2, J11.4, J21.4, J31.4, J41.4, U2.2
BUCK_SW: D2.1, L1.1, U1.2
B_ENC_A_RAW: J41.5, R41.1
B_ENC_B_RAW: J41.6, R43.1
B_ILIM: R40.1, U40.4
B_M1: J41.1, U40.6
B_M2: J41.2, U40.8
B_SERVO: J40.3, R45.2
F_ENC_A_RAW: J31.5, R31.1
F_ENC_B_RAW: J31.6, R33.1
F_ILIM: R30.1, U30.4
F_M1: J31.1, U30.6
F_M2: J31.2, U30.8
F_SERVO: J30.3, R35.2
GATE: DZ1.2, Q1.4, R1.1
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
